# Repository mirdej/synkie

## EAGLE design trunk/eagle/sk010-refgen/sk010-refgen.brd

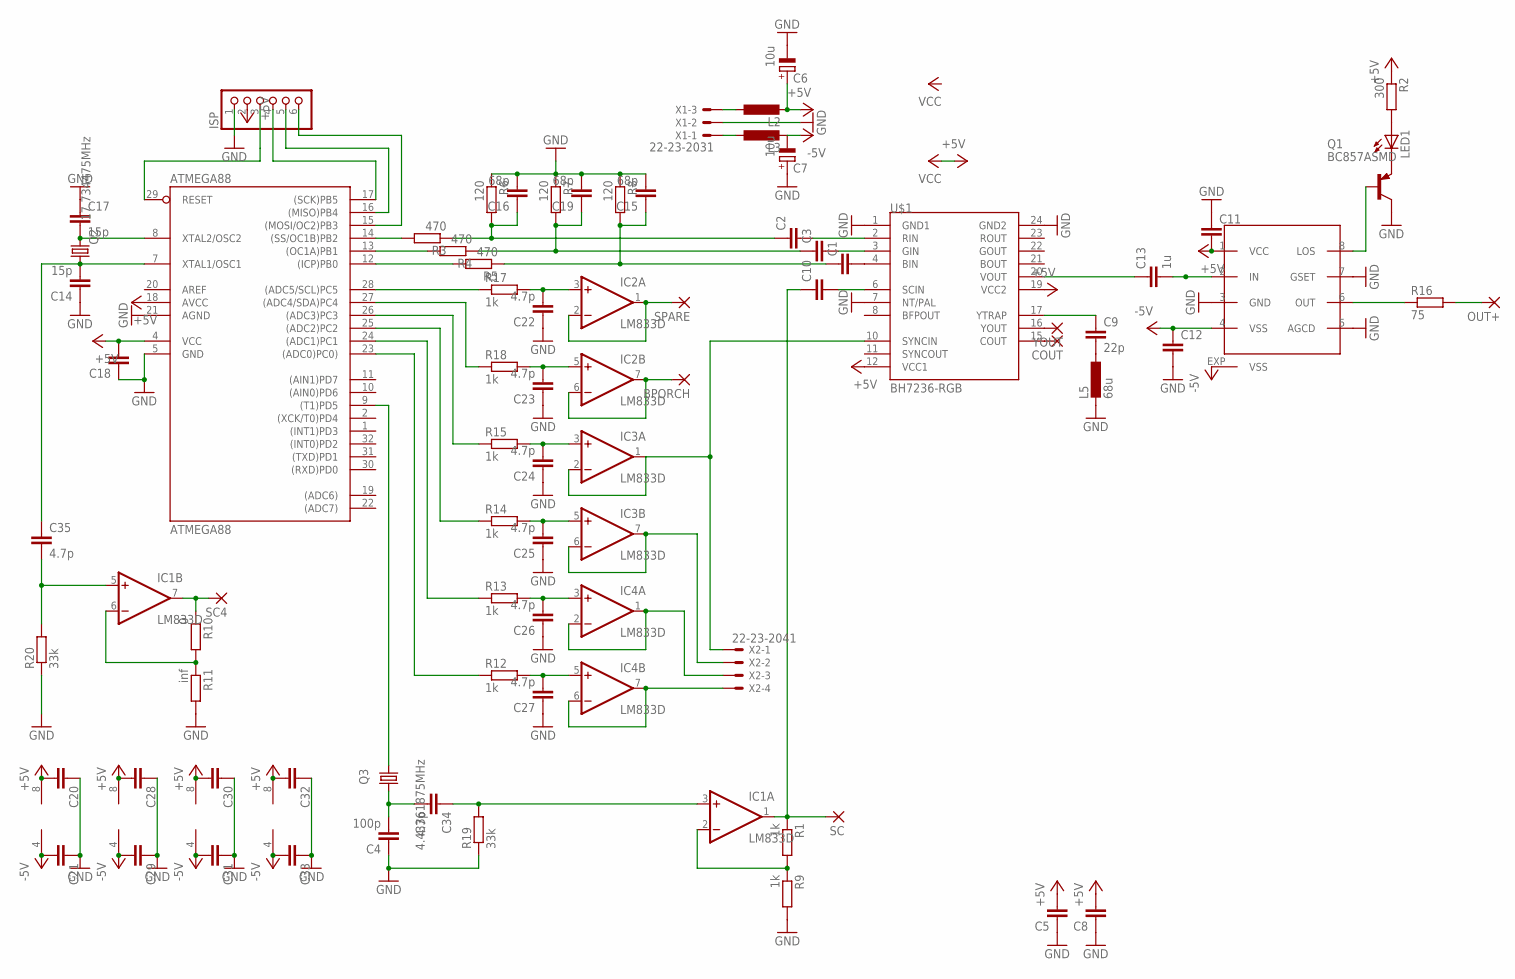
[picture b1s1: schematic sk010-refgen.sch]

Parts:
ATMEGA88: ATMEGA88; TQFP32-08
BPORCH: 3,17/1,1
C1, C2, C3, C10, C11, C12: C-EUC1206; C1206
C4: 100p; C1206
C5, C8, C18, C20, C21, C28, C29, C30, C31, C32, C33: C-EUC0603; C0603
C6, C7: 10u; CT3528
C9: 22p; C1206
C13: 1u; C1206
C14, C17: 15p; C1206
C15, C16, C19: 68p; C1206
C22, C23, C24, C25, C26, C27, C34, C35: 4.7p; C1206
COUT: 3,17/1,1
IC1, IC2, IC3, IC4: LM833D; SO08
ISP: PINHD-1X6; 1X06
L2, L3: L-EUL5038P; L5038P
L5: 68u; L5038P
LED1: LED3MM
OUT+: 3,17/1,1
Q1: BC857ASMD; SOT23-BEC
Q2: 17.734475MHz; HC49UP
Q3: 4.43361875MHz; HC49UP
R1, R9, R12, R13, R14, R15, R17, R18: 1k; R1206
R2: 300; R1206
R3, R4, R5: 470; R1206
R6, R7, R8: 120; R1206
R10: 0; R1206
R11: inf; R1206
R16: 75; R1206
R19, R20: 33k; R1206
SC, SC4: 3,17/1,1
SPARE: 3,17/1,1
U$1: BH7236-RGB; SO24N
U$2: MAX7450; SO08-EXP
X1: 22-23-2031
X2: 22-23-2041
YOUT: 3,17/1,1

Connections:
+5V: ATMEGA88.4 (VCC), ATMEGA88.18 (AVCC), C5.2, C6.+, C8.2, C11.2, C18.2, C20.2, C28.2, C30.2, C32.2, IC1.8 (V+), IC2.8 (V+), IC3.8 (V+), IC4.8 (V+), ISP.2, L2.2, R2.1, U$1.12 (VCC1), U$1.19 (VCC2), U$2.1 (VCC)
-5V: C7.-, C12.1, C21.2, C29.2, C31.2, C33.2, IC1.4 (V-), IC2.4 (V-), IC3.4 (V-), IC4.4 (V-), L3.2, U$2.4 (VSS), U$2.EXP (VSS)
AREF: ATMEGA88.20 (AREF)
GND: ATMEGA88.5 (GND), ATMEGA88.21 (AGND), C4.1, C5.1, C6.-, C7.+, C8.1, C11.1, C12.2, C14.1, C15.2, C16.2, C17.1, C18.1, C19.2, C20.1, C21.1, C22.1, C23.1, C24.1, C25.1, C26.1, C27.1, C28.1, C29.1, C30.1, C31.1, C32.1, C33.1, ISP.1, L5.2, Q1.C, R6.1, R7.1, R8.1, R9.2, R11.2, R19.1, R20.1, U$1.1 (GND1), U$1.7 (NT/PAL), U$1.24 (GND2), U$2.3 (GND), U$2.5 (AGCD), U$2.7 (GSET), X1.2
MISO: ATMEGA88.16 ((MISO)PB4), ISP.5
MOSI: ATMEGA88.15 ((MOSI/OC2)PB3), ISP.6
unnamed: C1.2, U$1.4 (BIN)
unnamed: ATMEGA88.9 ((T1)PD5), Q3.2
unnamed: C2.2, U$1.2 (RIN)
unnamed: C3.2, U$1.3 (GIN)
unnamed: C9.1, U$1.17 (YTRAP)
unnamed: C9.2, L5.1
unnamed: IC2.1 (OUT), IC2.2 (-IN), SPARE.1
unnamed: ATMEGA88.14 ((SS/OC1B)PB2), R3.2
unnamed: C22.2, IC2.3 (+IN), R17.2
unnamed: ATMEGA88.13 ((OC1A)PB1), R4.2
unnamed: L2.1, X1.3
unnamed: C10.2, U$1.6 (SCIN)
unnamed: IC1.6 (-IN), R10.2, R11.1
unnamed: Q1.B, U$2.8 (LOS)
unnamed: L3.1, X1.1
unnamed: LED1.A, R2.2
unnamed: ATMEGA88.29 (RESET), ISP.3
unnamed: LED1.K (C), Q1.E
unnamed: C13.2, U$2.2 (IN)
unnamed: ATMEGA88.12 ((ICP)PB0), R5.2
unnamed: BPORCH.1, IC2.6 (-IN), IC2.7 (OUT)
unnamed: IC1.7 (OUT), R10.1, SC4.1
unnamed: C4.2, C34.2, Q3.1
unnamed: C10.1, IC1.1 (OUT), R1.1, SC.1
unnamed: U$1.16 (YOUT), YOUT.1
unnamed: IC3.1 (OUT), IC3.2 (-IN), U$1.10 (SYNCIN), X2.1
unnamed: IC3.6 (-IN), IC3.7 (OUT), X2.2
unnamed: IC1.2 (-IN), R1.2, R9.1
unnamed: COUT.1, U$1.15 (COUT)
unnamed: IC4.1 (OUT), IC4.2 (-IN), X2.3
unnamed: R16.1, U$2.6 (OUT)
unnamed: OUT+.1, R16.2
unnamed: ATMEGA88.7 (XTAL1/OSC1), C14.2, C35.1, Q2.1
unnamed: C1.1, C15.1, R5.1, R8.2
unnamed: C2.1, C16.1, R3.1, R6.2
unnamed: C3.1, C19.1, R4.1, R7.2
unnamed: ATMEGA88.28 ((ADC5/SCL)PC5), R17.1
unnamed: C34.1, IC1.3 (+IN), R19.2
unnamed: ATMEGA88.27 ((ADC4/SDA)PC4), R18.1
unnamed: ATMEGA88.26 ((ADC3)PC3), R15.1
unnamed: ATMEGA88.25 ((ADC2)PC2), R14.1
unnamed: C13.1, U$1.20 (VOUT)
unnamed: IC4.6 (-IN), IC4.7 (OUT), X2.4
unnamed: ATMEGA88.24 ((ADC1)PC1), R13.1
unnamed: ATMEGA88.23 ((ADC0)PC0)), R12.1
unnamed: C24.2, IC3.3 (+IN), R15.2
unnamed: C25.2, IC3.5 (+IN), R14.2
unnamed: C26.2, IC4.3 (+IN), R13.2
unnamed: C23.2, IC2.5 (+IN), R18.2
unnamed: C27.2, IC4.5 (+IN), R12.2
unnamed: ATMEGA88.8 (XTAL2/OSC2), C17.2, Q2.2
unnamed: C35.2, IC1.5 (+IN), R20.2
SCK: ATMEGA88.17 ((SCK)PB5), ISP.4

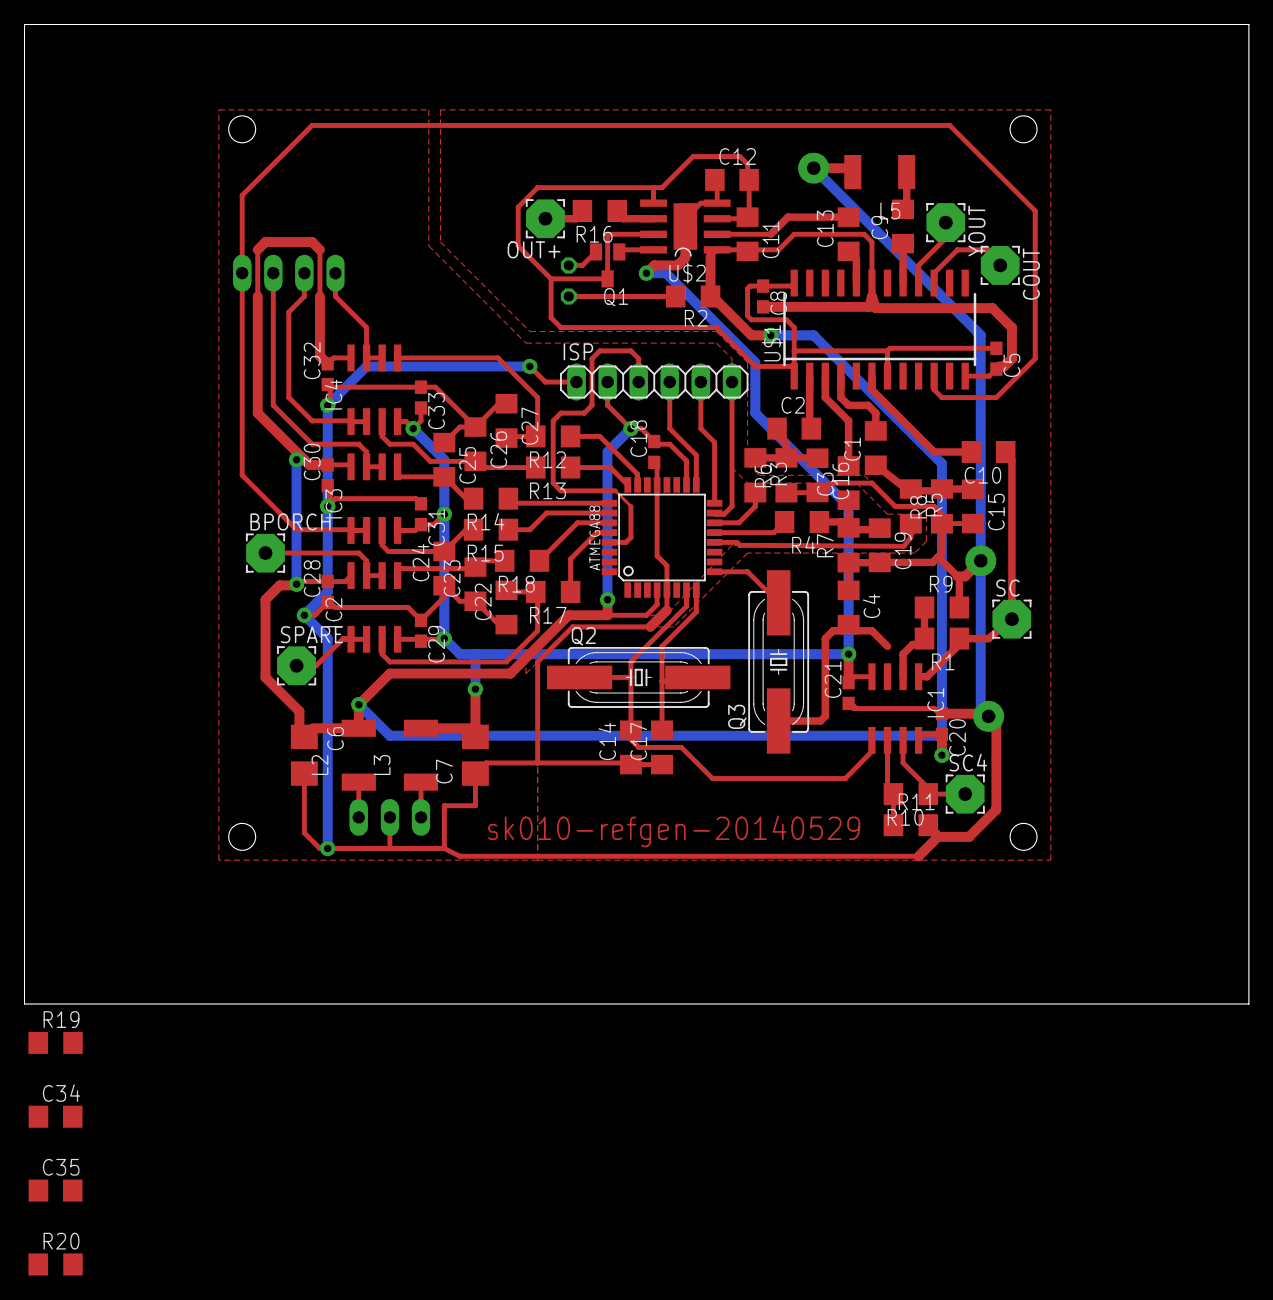
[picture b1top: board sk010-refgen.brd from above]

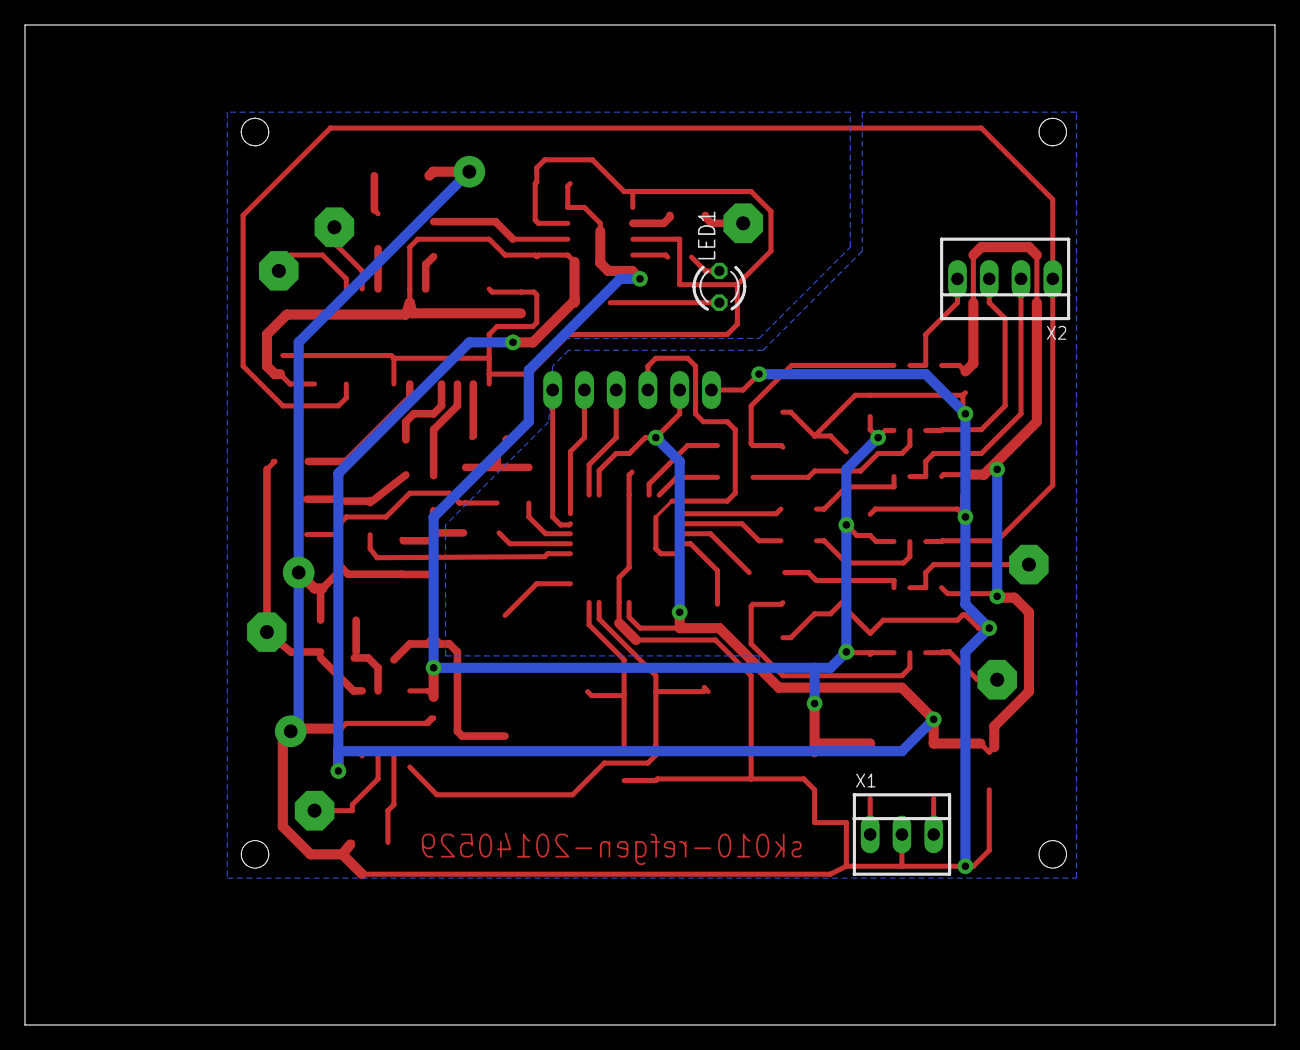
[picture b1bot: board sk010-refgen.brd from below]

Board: 2 copper layers, 100.0 x 80.0 mm, 79 parts (3 on the bottom side), 58 nets.

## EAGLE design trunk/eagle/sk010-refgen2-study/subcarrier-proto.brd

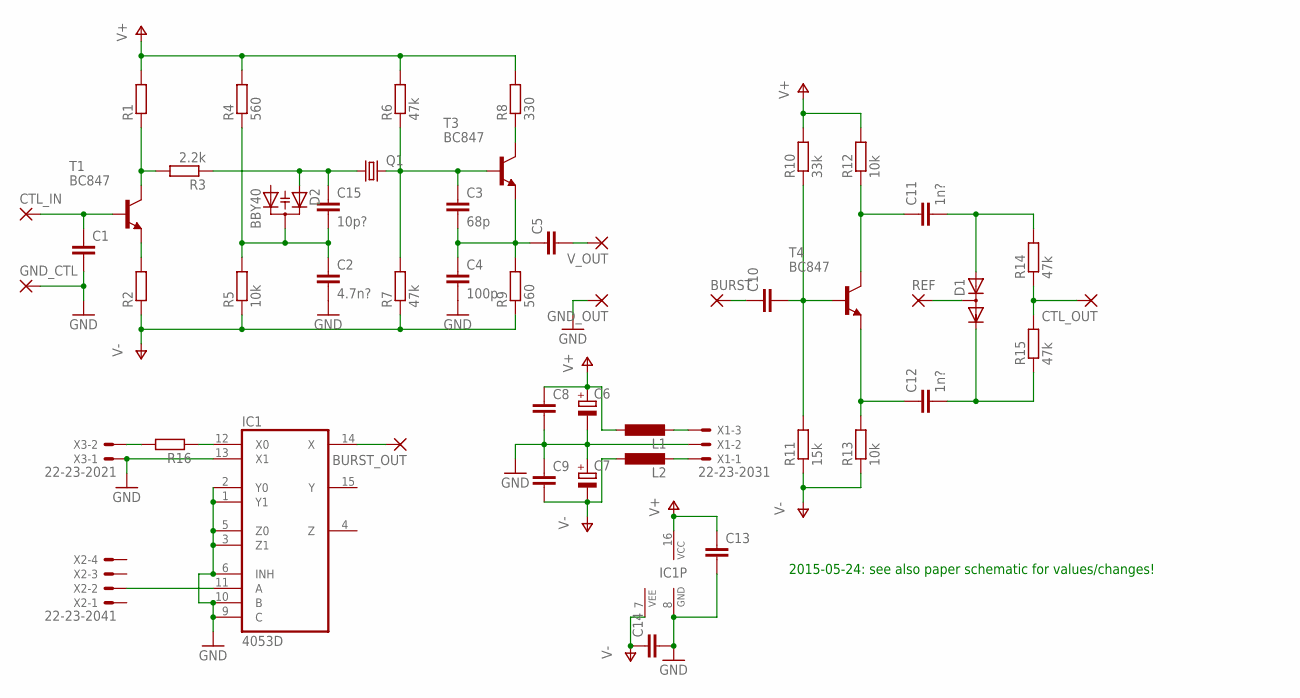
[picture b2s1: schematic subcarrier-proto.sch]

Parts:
BURST: WIREPAD3,17/1,1; 3,17/1,1
BURST_OUT: 3,17/1,1
C1, C5, C10: C-EUC1210; C1210
C2: 4.7n?; C1210
C3: 68p; C1210
C4: 100p; C1210
C6, C7: CPOL-EUCT3528; CT3528
C8, C9, C13, C14: C-EUC0805; C0805
C11, C12: 1n?; C1210
C15: 10p?; C1210
CTL_IN: WIREPAD3,17/1,1; 3,17/1,1
CTL_OUT: 3,17/1,1
D1: DIODE_2CACA-SOT23; SOT23
D2: BBY40; SOT23
GND_CTL: WIREPAD3,17/1,1; 3,17/1,1
GND_OUT: 3,17/1,1
IC1: 4053D; SO16
L1, L2: L-EUL5038P; L5038P
Q1: CRYSTALHC49UP; HC49UP
R1, R2, R16: R-EU_R1210; R1210
R3: 2.2k; R1210
R4, R9: 560; R1210
R5, R12, R13: 10k; R1210
R6, R7, R14, R15: 47k; R1210
R8: 330; R1210
R10: 33k; R1210
R11: 15k; R1210
REF: 3,17/1,1
T1, T3, T4: BC847; SOT23
V_OUT: 3,17/1,1
X1: 22-23-2031
X2: 22-23-2041
X3: 22-23-2021

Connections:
GND: C1.2, C2.2, C4.2, C6.-, C7.+, C8.2, C9.1, C13.2, C14.2, GND_CTL.1, GND_OUT.1, IC1.1 (Y1), IC1.2 (Y0), IC1.3 (Z1), IC1.5 (Z0), IC1.6 (INH), IC1.8 (GND), IC1.9 (C), IC1.10 (B), IC1.13 (X1), X1.2, X3.1
unnamed: C1.1, CTL_IN.1, T1.1 (B)
unnamed: C5.2, V_OUT.1
unnamed: R1.1, R3.2, T1.3 (C)
unnamed: R2.2, T1.2 (E)
unnamed: C2.1, C15.2, D2.3 (C), R4.1, R5.2
unnamed: C15.1, D2.1 (A1), Q1.1, R3.1
unnamed: L1.2, X1.3
unnamed: L2.2, X1.1
unnamed: C3.1, Q1.2, R6.1, R7.2, T3.1 (B)
unnamed: R8.1, T3.3 (C)
unnamed: C3.2, C4.1, C5.1, R9.2, T3.2 (E)
unnamed: BURST.1, C10.1
unnamed: C10.2, R10.1, R11.2, T4.1 (B)
unnamed: C12.1, R13.2, T4.2 (E)
unnamed: C11.1, R12.1, T4.3 (C)
unnamed: C11.2, D1.1 (A), R14.2
unnamed: C12.2, D1.2 (C), R15.1
unnamed: CTL_OUT.1, R14.1, R15.2
unnamed: IC1.12 (X0), R16.1
unnamed: D1.3 (AC), REF.1
unnamed: R16.2, X3.2
unnamed: IC1.11 (A), X2.2
unnamed: BURST_OUT.1, IC1.14 (X)
V+: C6.+, C8.1, C13.1, IC1.16 (VCC), L1.1, R1.2, R4.2, R6.2, R8.2, R10.2, R12.2
V-: C7.-, C9.2, C14.1, IC1.7 (VEE), L2.1, R2.1, R5.1, R7.1, R9.1, R11.1, R13.1

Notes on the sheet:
2015-05-24: see also paper schematic for values/changes!

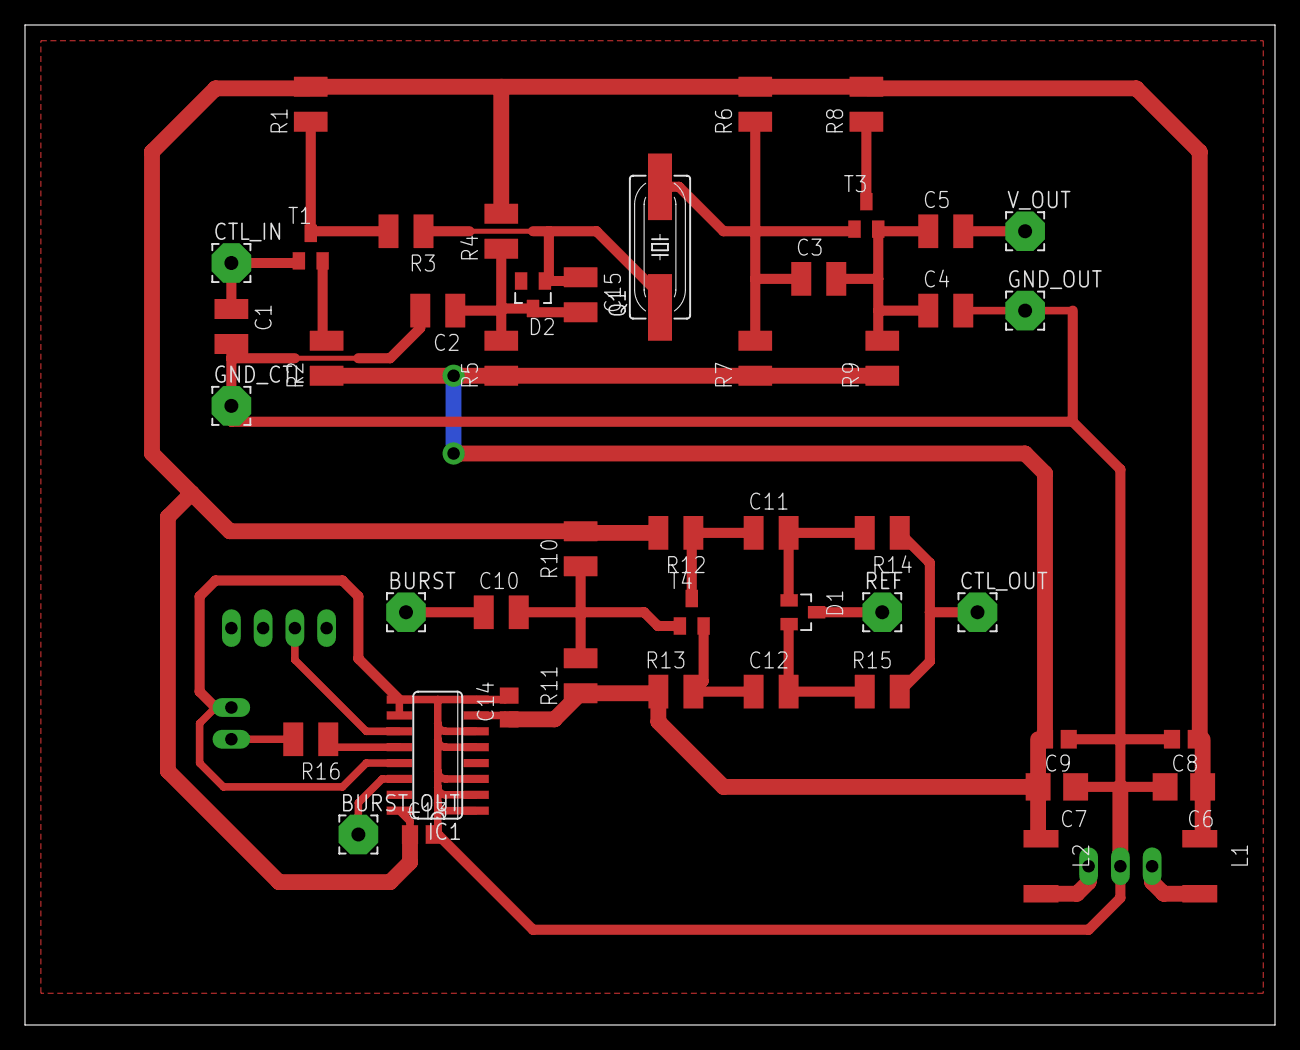
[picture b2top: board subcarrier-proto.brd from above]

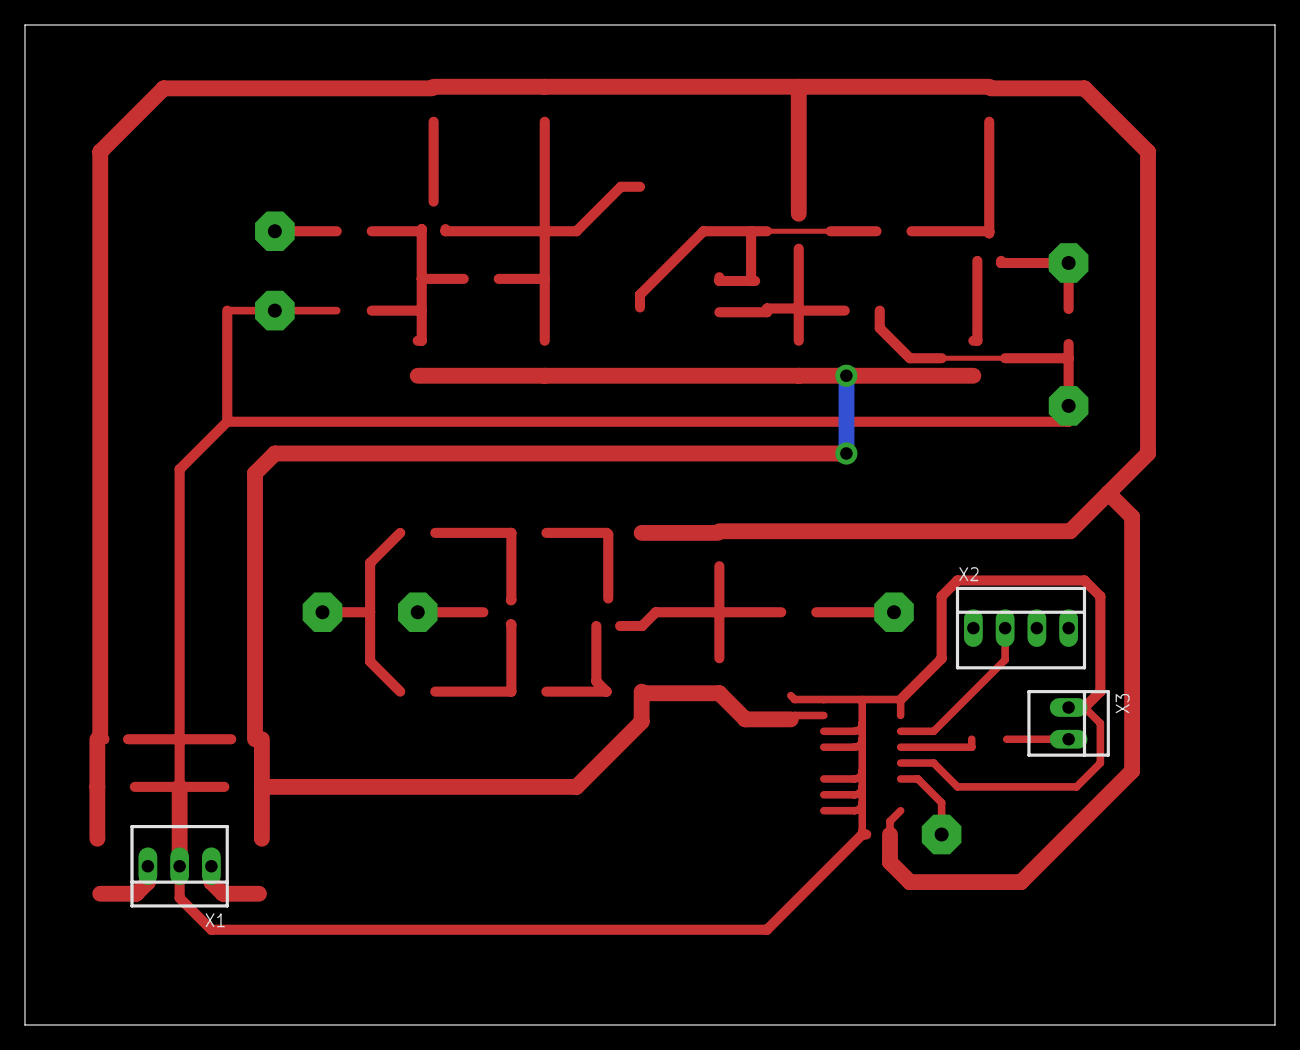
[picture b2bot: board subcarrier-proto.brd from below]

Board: 2 copper layers, 100.0 x 80.0 mm, 51 parts (3 on the bottom side), 26 nets.

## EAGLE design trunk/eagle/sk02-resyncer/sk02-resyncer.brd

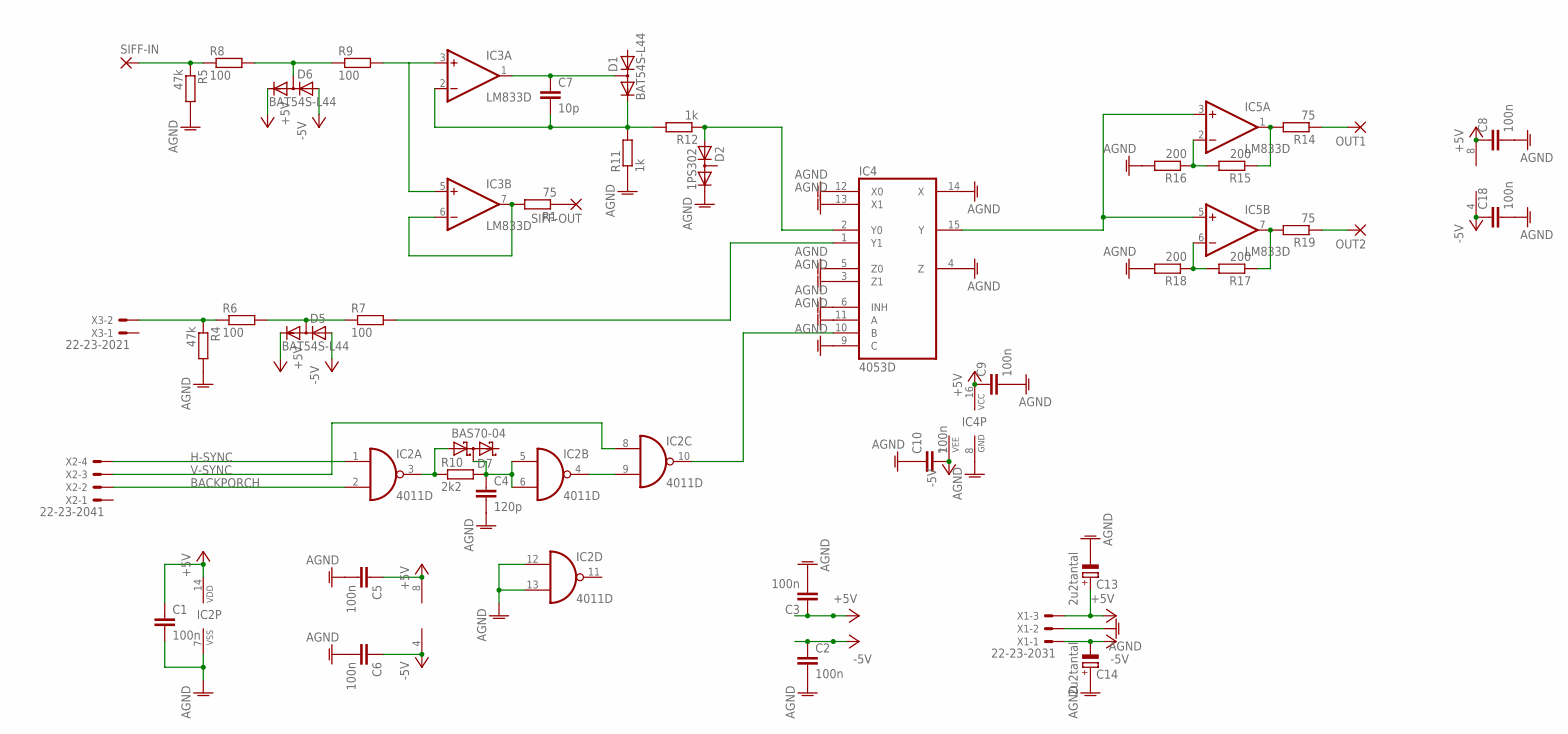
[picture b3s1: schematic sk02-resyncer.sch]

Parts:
C1, C2, C3, C5, C6: 100n; C1206
C4: 120p; C1206
C7: 10p; C1206
C8, C9, C10, C18: 100n; C0805
C13, C14: 2u2tantal; CT3528
D1, D5, D6: BAT54S-L44; SOT23
D2: 1PS302; SOT23
D7: BAS70-04; SOT23
IC2: 4011D; SO14
IC3, IC5: LM833D; SO08
IC4: 4053D; SO16
OUT1, OUT2: 3,17/1,1
R1, R14, R19: 75; R1206
R4, R5: 47k; R1206
R6, R7, R8, R9: 100; R1206
R10: 2k2; R1206
R11, R12: 1k; R1206
R15, R16, R17, R18: 200; R1206
SIFF-IN: 3,17/1,1
SIFF-OUT: 3,17/1,1
X1: 22-23-2031
X2: 22-23-2041
X3: 22-23-2021

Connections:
+5V: C1.1, C3.1, C5.1, C8.1, C9.1, C13.+, D5.2 (C), D6.2 (C), IC2.14 (VDD), IC3.8 (V+), IC4.16 (VCC), IC5.8 (V+), X1.3
-5V: C2.1, C6.1, C10.2, C14.-, C18.1, D5.1 (A), D6.1 (A), IC3.4 (V-), IC4.7 (VEE), IC5.4 (V-), X1.1
AGND: C1.2, C2.2, C3.2, C4.2, C5.2, C6.2, C8.2, C9.2, C10.1, C13.-, C14.+, C18.2, D2.2 (C), IC2.7 (VSS), IC2.12 (I0), IC2.13 (I1), IC4.3 (Z1), IC4.4 (Z), IC4.5 (Z0), IC4.6 (INH), IC4.8 (GND), IC4.9 (C), IC4.11 (A), IC4.12 (X0), IC4.13 (X1), IC4.14 (X), R4.2, R5.2, R11.1, R16.2, R18.2, X1.2
BACKPORCH: IC2.2 (I1), X2.2
H-SYNC: IC2.1 (I0), X2.4
unnamed: IC3.6 (-IN), IC3.7 (OUT), R1.2
unnamed: R4.1, R6.1, X3.2
unnamed: D5.3 (AC), R6.2, R7.1
unnamed: C4.1, D7.3 (C1A2), IC2.5 (I0), IC2.6 (I1), R10.2
unnamed: IC4.1 (Y1), R7.2
unnamed: D2.1 (A), IC4.2 (Y0), R12.1
unnamed: IC2.4 (O), IC2.9 (I1)
unnamed: D7.1 (A1), IC2.3 (O), R10.1
unnamed: R1.1, SIFF-OUT.1
unnamed: IC3.3 (+IN), IC3.5 (+IN), R9.2
unnamed: IC2.10 (O), IC4.10 (B)
unnamed: C7.1, D1.3 (AC), IC3.1 (OUT)
unnamed: R5.1, R8.1, SIFF-IN.1
unnamed: D6.3 (AC), R8.2, R9.1
unnamed: C7.2, D1.2 (C), IC3.2 (-IN), R11.2, R12.2
unnamed: IC5.2 (-IN), R15.2, R16.1
unnamed: IC5.1 (OUT), R14.2, R15.1
unnamed: IC4.15 (Y), IC5.3 (+IN), IC5.5 (+IN)
unnamed: IC5.6 (-IN), R17.2, R18.1
unnamed: IC5.7 (OUT), R17.1, R19.2
unnamed: OUT1.1, R14.1
unnamed: OUT2.1, R19.1
V-SYNC: IC2.8 (I0), X2.3

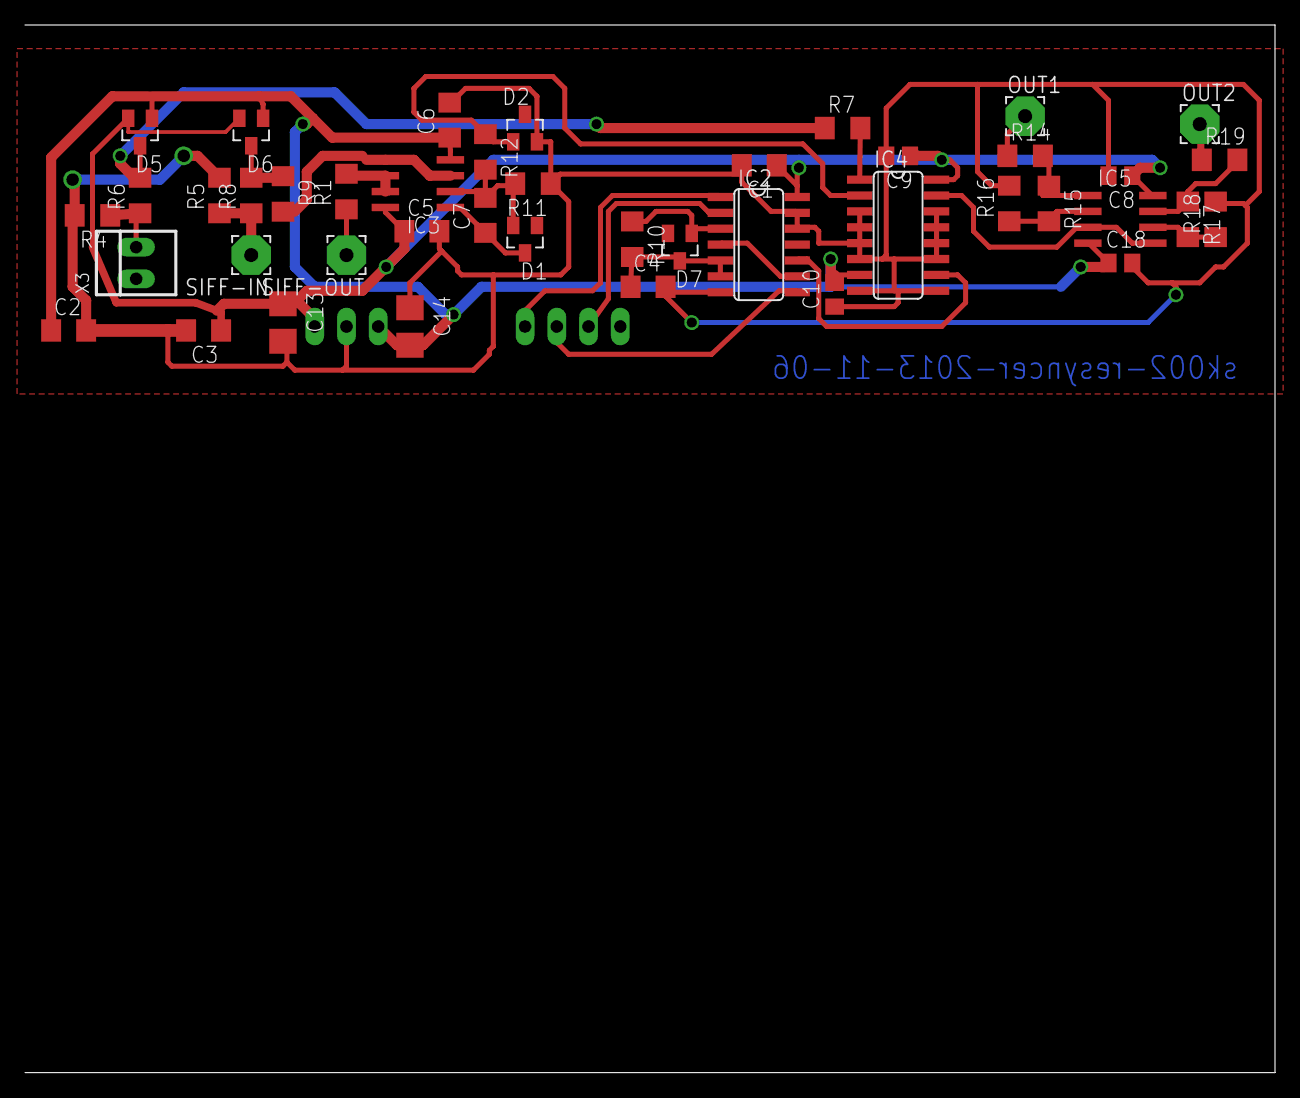
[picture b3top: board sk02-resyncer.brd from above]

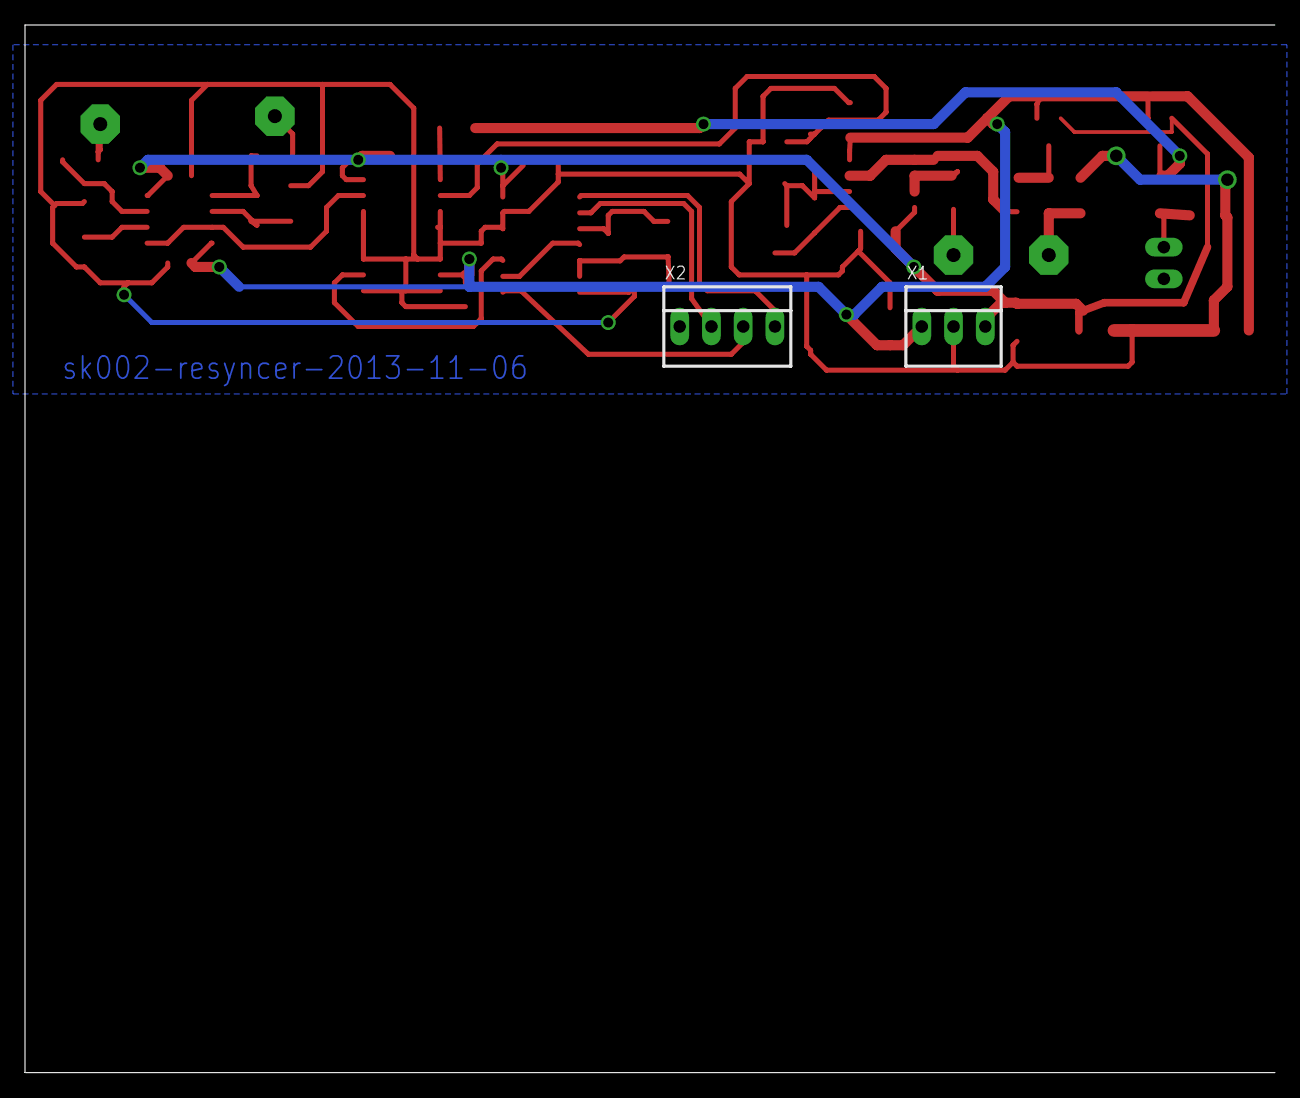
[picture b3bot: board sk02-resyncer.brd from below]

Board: 2 copper layers, 100.0 x 83.8 mm, 45 parts (2 on the bottom side), 28 nets.
